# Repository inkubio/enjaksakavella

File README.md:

# Enjaksakavella

This is a project to control an electric wheelchair with custom controllers.

Project parts:
- Electronics connecting to wheelchair
- BLE-enabled Arduino driving the electronics
- Computer with software which handles:
  - BLE connection to Arduino
  - Connection to controllers
  - Visualizing controller working principles
  - Visualizing commands sent to wheelchair
- Custom controller(s)
  - Cap with eye-tracking camera

## Requirements

### Python Packages
- General (Qt)
  - PySide2
- Bluetooth on Linux
  - pydbus
  - python3-gi (from distribution repositories)
  - vext
  - vext<span></span>.gi (for python3-gi)
- For Eyetracker controller
  - OpenCV2
  - numpy

### Arduino Libraries:
- ArduinoBLE

## Documentation

More documentation can be found in /doc folder

## Quick Start Guide
Using a laptop with linux and BLE-capable bluetooth

### Install software on computer

1. Clone the git repository

        git clone https://github.com/inkubio/enjaksakavella.git

2. Create a new virtual environment for the project and activate it

        cd enjaksakavella
        python3 -m venv .venv
        source .venv/bin/activate

    When running the program, remember activate this virtual environment first by running the activate script.

3. Install required software, with python packages in the virtual environment

    For Qt:

        pip3 install pyside2

    For DBus:

        pip3 install pydbus

    For DBus error handling use system's GObject Inspector since the packages can't be found on pip. First, ensure that you have python3-gi installed:

        sudo apt install python3-gi

    For compiling python modules:

        sudo apt install python3-dev

    For Qt wayland support:
        sudo apt install qtwayland5

    Then install vext package to use python3-gi

        pip3 install vext --no-binary :all:
        pip3 install vext.gi --no-binary :all:

    For Eyetracker: (opencv-python also installs numpy)

        pip3 install opencv-python

    For acceleration glasses:
        pip3 install phidget22

        Additionally, install the libphidget22 library to /usr/lib, for example by following these compile instructions: https://www.phidgets.com/docs/OS_-_Linux#Source%20Install . Remember to also add the udev-rule!

    Check that you get something like this with `pip3 list` and the setup should be done.

        (.venv) tuomas@blini:~/Ohjelmointi/enjaksakavella/src$ pip3 list
        Package          Version 
        ---------------- --------
        numpy            1.22.3
        opencv-python    4.5.5.64
        Phidget22        1.10.20220211
        pip              20.3.4
        pkg-resources    0.0.0
        pydbus           0.6.0
        PySide2          5.15.2.1
        ruamel.yaml      0.17.21
        ruamel.yaml.clib 0.2.6
        setuptools       44.1.1
        shiboken2        5.15.2.1
        vext             0.7.6
        vext.gi          0.7.4

### Control the wheelchair
1. Connect the electronics to RNET OMNI's port 1
2. Turn on the wheelchair from RNET OMNI
3. Set control program to 3 from RNET OMNI
4. Run `main.py` in `src` folder
  - You may need to specify using Wayland on newer OS versions: `python main.py -platform wayland`
5. Select Bluetooth wheelchair and click connect
6. Select your favourite controller from the GUI
7. Enable desired movement(s) from the GUI
8. Move around without the need to use your legs

You should see this after step 3:

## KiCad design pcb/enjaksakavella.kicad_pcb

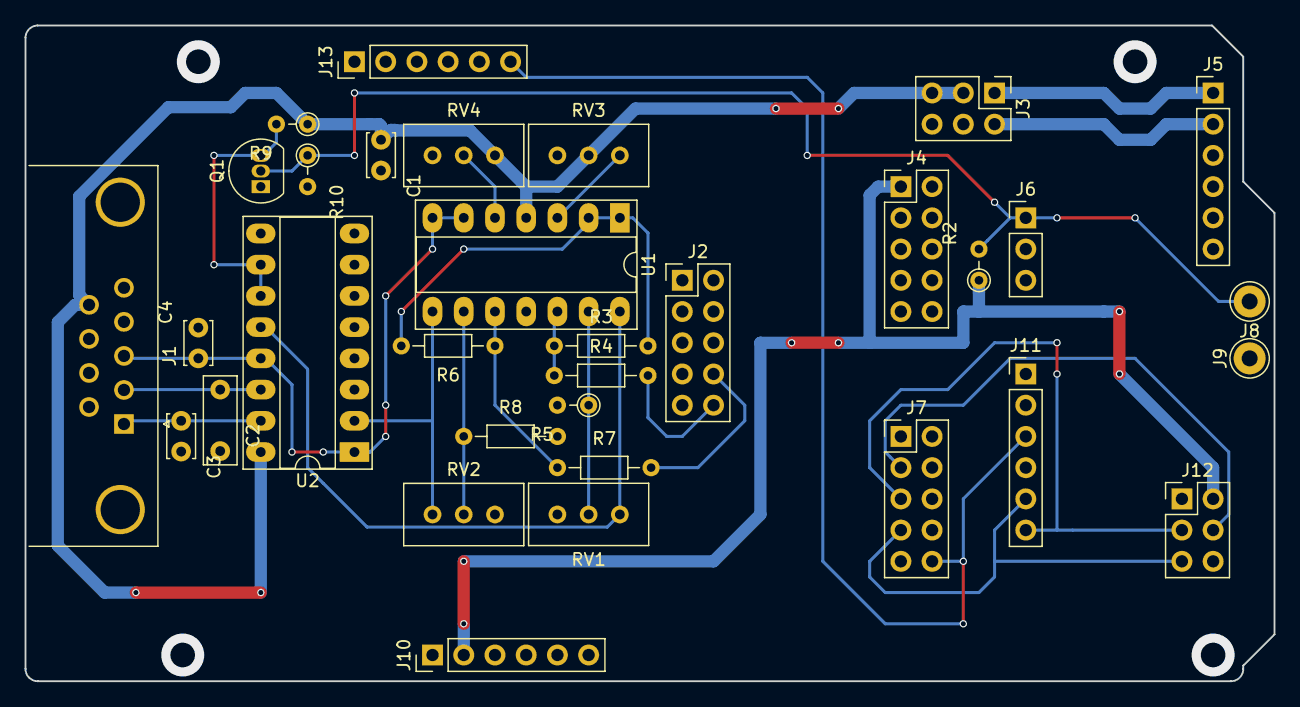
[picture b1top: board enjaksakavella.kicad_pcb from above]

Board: 2 copper layers, 101.6 x 53.3 mm, 33 parts (0 on the bottom side), 25 nets.

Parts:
C1, C3, C4: 0.1u; C_Disc_D3.4mm_W2.1mm_P2.50mm
C2: 0.1u; C_Disc_D7.0mm_W2.5mm_P5.00mm
J1: DB9_Female; DSUB-9_Female_Horizontal_P2.77x2.84mm_EdgePinOffset4.94mm_H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
J2, J4, J7: Conn_02x05_Odd_Even; PinHeader_2x05_P2.54mm_Vertical
J3, J12: Conn_02x03_Odd_Even; PinHeader_2x03_P2.54mm_Vertical
J5, J10, J11, J13: Conn_01x06; PinHeader_1x06_P2.54mm_Vertical
J6: Conn_01x03; PinHeader_1x03_P2.54mm_Vertical
J8, J9: Conn_01x01; Pin_D1.3mm_L11.0mm
Q1: 2N7000; TO-92_Inline
R2, R9, R10: 10k; R_Axial_DIN0204_L3.6mm_D1.6mm_P2.54mm_Vertical
R3, R6: 47k; R_Axial_DIN0204_L3.6mm_D1.6mm_P7.62mm_Horizontal
R4, R7, R8: 39k; R_Axial_DIN0204_L3.6mm_D1.6mm_P7.62mm_Horizontal
R5: 39k; R_Axial_DIN0204_L3.6mm_D1.6mm_P2.54mm_Vertical
RV1, RV2, RV3, RV4: 50k; Potentiometer_Bourns_3296W_Vertical
U1: LM324; DIP-14_W7.62mm_Socket_LongPads
U2: 4053; DIP-16_W7.62mm_Socket_LongPads

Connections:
+3V3: J4.1, J10.2, J12.2, R2.1
+12V: C1.1, J1.9, J3.3, J3.5, R9.1, RV3.2, RV4.1, U1.4, U2.16
/DAC_O1: J2.10, R4.2
/DAC_O2: J2.8, R7.2
/DIR: C2.1, J1.2, U2.14
/J_DIR: RV1.3, U1.14, U2.12
/J_REF: C4.1, J1.3, U1.6, U1.7, U2.1, U2.13
/J_SPEED: RV2.3, U1.8, U2.2
/MISO: J7.5, J11.6, J12.3
/MOSI: J7.7, J11.5, J12.5
/OFFSET: R3.2, R6.2, U1.1, U1.2
/SCK: J7.3, J12.4
/SPEED: C3.1, J1.1, U2.15
/SS: J7.10, J11.3, J13.6
/STOP: J6.1, J8.1, Q1.2, R2.2, R10.1
GND: C1.2, C2.2, C3.2, C4.2, J1.4, J1.5, J1.6, J1.8, J3.4, J3.6, J4.6, J9.1, J10.4, J10.5, Q1.1, R5.2, R8.2, R10.2, RV3.3, RV4.3, U1.11, U2.6, U2.7, U2.8
unnamed: J3.1, J5.1
unnamed: J3.2, J5.2
unnamed: Q1.3, R9.2, U2.10, U2.11
unnamed: R3.1, R4.1, U1.12
unnamed: R5.1, RV1.2, U1.13
unnamed: R6.1, R7.1, U1.10
unnamed: R8.1, RV2.2, U1.9
unnamed: RV3.1, U1.3
unnamed: RV4.2, U1.5

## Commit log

2020-02-18 Added rest of the system parts
2020-02-18 Added initial PCB schematics
2020-02-18 Added TODO list
2020-02-19 Moved some TODOs from documentation
2020-02-19 Updated documentation to reflect current system
2020-04-07 Use bluetooth with dbus
2020-04-08 Add installation instructions
2020-04-08 Update documentation
2020-04-08 Update TODO
2020-04-09 Add .gitignore
2020-04-09 Add indication that the software is attempting to connect
2020-04-09 Remove an "s" left behind
2020-04-10 Fix crash when quitting program
2020-04-11 Improve exception handling
2020-04-11 Add platform-specific BLE connection implementation
2020-04-21 Change EDA software (and file format) from EAGLE to KiCad
2022-03-16 Update instructions for newer OS versions
2022-03-16 Prevent infinite loop if closing app while connecting with BLE
2022-03-16 Release keys automatically
2022-03-21 Improve responsiveness
2022-03-21 Make bluetooth communication non-blocking
2022-03-25 Update pcb files to new KiCad version
2022-03-25 Add accelerometer glasses controller
2022-03-25 Add Phidget22 to pip list example
2022-03-25 Add libphidget22.so to repo
2022-03-25 Fix instructions for installing libphidget22
2022-03-25 Add reminder for installing the udev rules
